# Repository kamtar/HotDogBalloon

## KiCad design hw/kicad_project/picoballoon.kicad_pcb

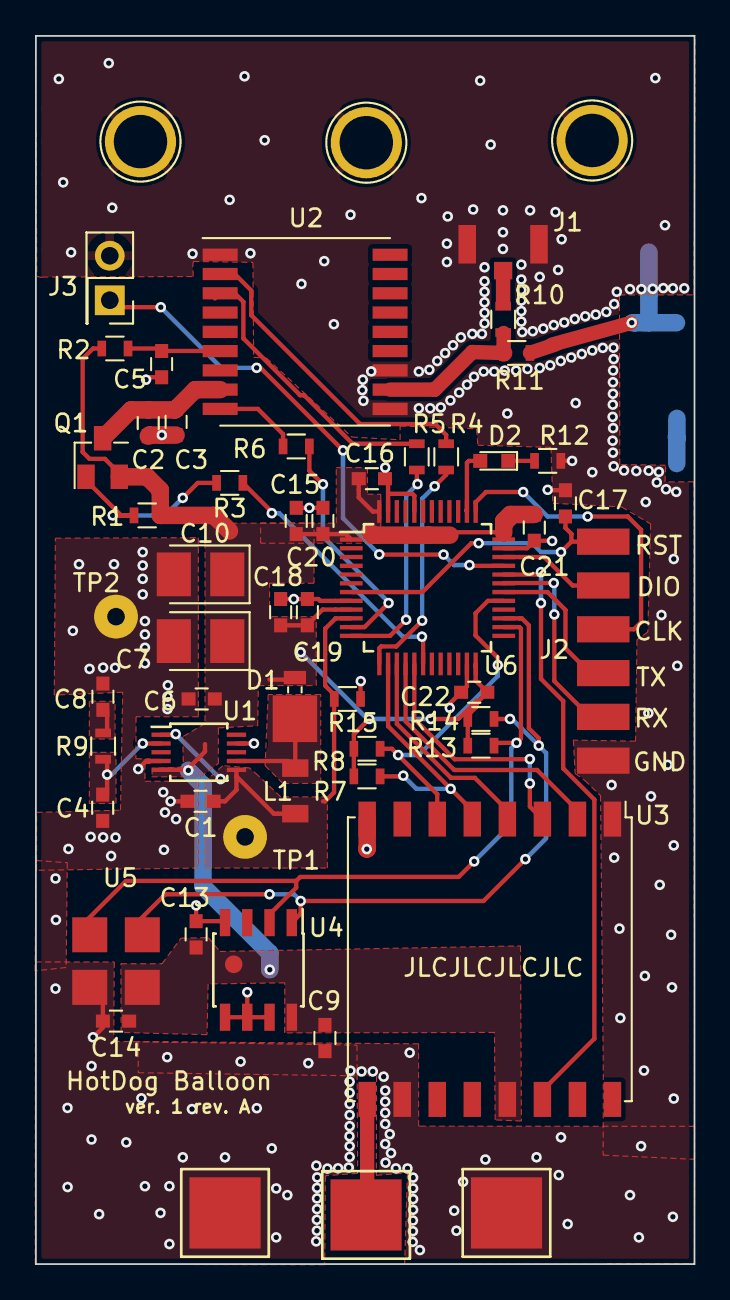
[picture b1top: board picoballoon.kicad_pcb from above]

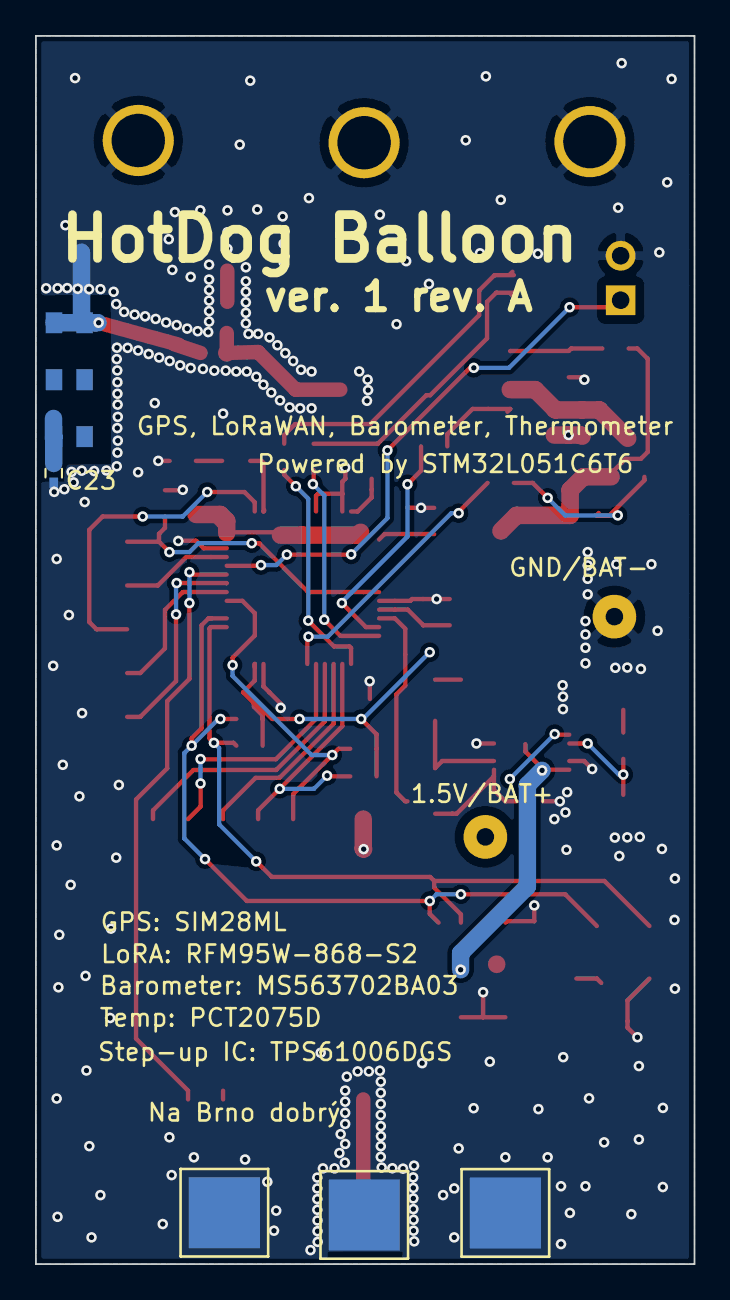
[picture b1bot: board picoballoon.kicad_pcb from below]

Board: 2 copper layers, 37.6 x 70.1 mm, 61 parts (5 on the bottom side), 36 nets.

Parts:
AE1: Antenna; 1Pin
ANT1: M830120
C1, C15: 10u; C_0603
C2, C9: 4.7u; C_0603
C3, C5, C6, C13, C14, C16, C17, C19, C20, C21, C22: 100n; C_0603
C4: 100p; C_0603
C7, C10: 100u; CP_Tantalum_Case-T_EIA-3528-12_Reflow
C8: 33n; C_0603
C18: 1u; C_0603
C23: 100p; C_0402
D1: MBRM120LT3G; D_Powermite_KA
D2: LED; LED_0603
J1: Conn_Coaxial; ufl
J2: DEBUG_CONN; DBG_CONN
J3: SYS_IN; Socket_Strip_Straight_2x01_Pitch2.54mm
L1: 33u; Inductor_2520
Q1: FDN306P; SuperSOT-3
R1: 1M; R_0603
R2: 0; R_0603
R3: 1k; R_0603
R4, R5: 100; R_0603
R6, R10, R15: none; R_0603
R7, R8, R9, R13, R14: 10k; R_0603
R11: 0R; R_0603
R12: 200; R_0603
TP1: BAT+; SolderWirePad_single_1mmDrill
TP2: BAT-; SolderWirePad_single_1mmDrill
TP3, TP4, TP8: DrillHole; 1pin
TP5, TP6, TP7, TP9, TP10: GND; 1Pin
U1: TPS61006; TSSOP-10_3x3mm_Pitch0.5mm
U2: SIM28ML
U3: RFM95W-868S2; HOPERF_RFM9XW_SMD
U4: PCT2075D; SOIC-8_3.9x4.9mm_Pitch1.27mm
U5: MS563702BA03; MS5637
U6: STM32L051C6Tx; LQFP-48_7x7mm_Pitch0.5mm

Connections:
+3V3: C6.1, C7.1, C9.1, C10.1, C13.1, C14.1, C15.1, C16.1, C18.1, C19.1, C20.1, C21.1, C22.1, D1.1, Q1.2, R1.1, R2.2, R7.2, R8.2, R13.1, R14.1, U1.5, U3.13, U4.8, U5.1, U6.1, U6.9, U6.24, U6.36, U6.48
/DBG_RX: J2.5, U6.31
/DBG_TX: J2.4, U6.30
/GPS_RESET: R6.2, U6.11
/GPS_RX: R4.2, U6.13
/GPS_TX: R5.2, U6.12
/GPS_VB: C5.2, R2.1, U2.6
/GPS_VCC: C2.1, C3.2, Q1.3, U2.8
/GPS_VCC_ON: R3.1, U6.18
/LORA_CS: R7.1, U3.5, U6.14
/LORA_RST: R8.1, U3.6, U6.29
/RST: C17.1, J2.1, U6.7
/SCL: R13.2, U4.2, U5.3, U6.26
/SDA: R14.2, U4.1, U5.2, U6.27
/SPI_MISO: U3.2, U6.16
/SPI_MOSI: U3.3, U6.17
/SPI_SCK: U3.4, U6.15
/SWCLK: J2.3, U6.37
/SWDIO: J2.2, U6.34
/SYS_INPUT: J3.1, U6.33
/SYS_LED: D2.2, U6.38
/TX_DONE: U3.14, U6.32
GND: ANT1.1, ANT1.6, C1.2, C2.2, C3.1, C4.2, C5.1, C6.2, C7.2, C8.2, C9.2, C10.2, C13.2, C14.2, C15.2, C16.2, C17.2, C18.2, C19.2, C20.2, C21.2, C22.2, C23.1, J1.2, J2.6, J3.2, R11.1, R12.1, R15.1, TP2.1, TP3.1, TP4.1, TP5.1, TP6.1, TP7.1, TP8.1, TP9.1, TP10.1, U1.4, U1.9, U2.1, U2.10, U2.12, U3.1, U3.8, U3.10, U4.4, U4.5, U4.6, U4.7, U5.4, U6.8, U6.23, U6.35, U6.44, U6.47
unnamed: AE1.1, U3.9
unnamed: ANT1.3, C23.2
unnamed: C4.1, R9.2, U1.2
unnamed: C8.1, R9.1
unnamed: D1.2, L1.2, U1.7
unnamed: D2.1, R12.2
unnamed: J1.1, R10.2
unnamed: Q1.1, R1.2, R3.2
unnamed: R4.1, U2.2
unnamed: R5.1, U2.3
unnamed: R6.1, U2.9
unnamed: R10.1, R11.2, U2.11
V_BATT: C1.1, L1.1, R15.2, TP1.1, U1.1, U1.6, U6.10

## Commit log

2019-01-26 first commit - eclipse atollic project
2019-02-02 generated some more code from stm gen code thingy (mainly SPI and AES) started fork on semtech126x added lorawanstack added dataref stuff
2019-03-23 ported lora files from atmel samD21 test..not tested!
2019-11-27 cmake attempt and new hardware in kicad
2019-12-02 minor consmetic changes
2019-12-02 updated pdf
2019-12-04 schematics rev.B
2019-12-04 bug R16 none -> 0
2019-12-09 deleted old project and added new one for stm32l0
2019-12-18 added lora driver
2019-12-18 no message
2019-12-27 Zakomentovano pouziti GPS Zmena hlavnich hodin z PLL na HSI 16 MHz Po inicializaci SX1276 prechod do STANDBY a nasledne do SLEEP WAIT nebo STOP na konci hlavni smycky RTC wakeup kazdou sekundu, blikn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
2019-12-28 Optimalizace spotreby
2020-01-12 Inicialiace externi flash, vycteni ID a write enable, priprava driveru
2020-01-25 Prikazy na systemovem UARTu k ovladani externi flash.
2020-01-25 Oprava probouzeni na spravne hodiny Definice timeoutu pro sys UART - po resetu 30s, prodluzovani pri komunikaci Zapinani/vypinani rozhrani UART1, SPI1
2020-02-02 Ovladani GPS, parsovani udaju, refaktoring
2020-02-02 Pravidelne eventy GPS, obnoveno usinani
2020-02-02 Mereni teploty Priprava na casovani vsech eventu Warm start misto hot start u GPS
